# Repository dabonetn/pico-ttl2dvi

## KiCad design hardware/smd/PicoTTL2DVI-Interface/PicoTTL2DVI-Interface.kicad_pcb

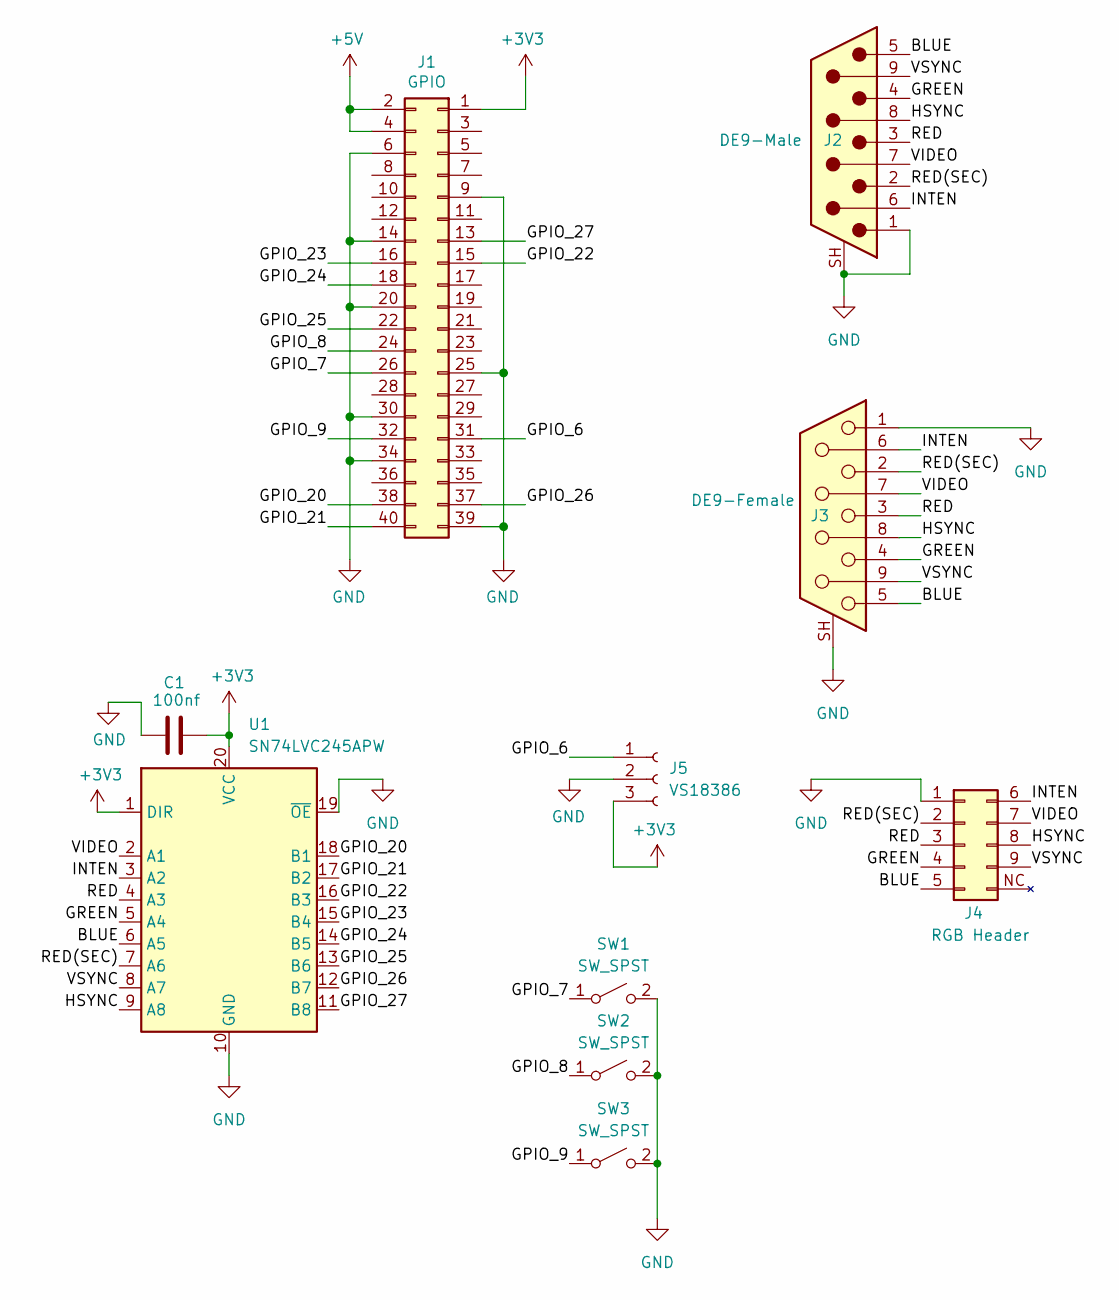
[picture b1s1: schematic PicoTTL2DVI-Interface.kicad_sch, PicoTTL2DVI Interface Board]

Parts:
C1: 100nf; C_0805_2012Metric_Pad1.18x1.45mm_HandSolder
J1: GPIO; PinSocket_2x20_P2.54mm_Vertical
J2: DE9-Male; DSUB-9_Pins_EdgeMount_P2.77mm
J3: DE9-Female; DSUB-9_Socket_EdgeMount_P2.77mm
J4: RGB Header; PinHeader_2x05_P2.54mm_Horizontal
J5: VS18386; PinHeader_1x03_P2.54mm_Vertical
SW1, SW2, SW3: SW_SPST; SW_PUSH_6mm
U1: SN74LVC245APW; TSSOP-20_4.4x6.5mm_P0.65mm

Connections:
+3V3: C1.2, J1.1, J5.3, U1.1 (DIR), U1.20 (VCC)
+5V: J1.2, J1.4
/BLUE: J2.5, J3.5, J4.5, U1.6 (A5)
/GPIO_6: J1.31, J5.1
/GPIO_7: J1.26, SW1.1 (A)
/GPIO_8: J1.24, SW2.1 (A)
/GPIO_9: J1.32, SW3.1 (A)
/GPIO_20: J1.38, U1.18 (B1)
/GPIO_21: J1.40, U1.17 (B2)
/GPIO_22: J1.15, U1.16 (B3)
/GPIO_23: J1.16, U1.15 (B4)
/GPIO_24: J1.18, U1.14 (B5)
/GPIO_25: J1.22, U1.13 (B6)
/GPIO_26: J1.37, U1.12 (B7)
/GPIO_27: J1.13, U1.11 (B8)
/GREEN: J2.4, J3.4, J4.4, U1.5 (A4)
/HSYNC: J2.8, J3.8, J4.8, U1.9 (A8)
/INTEN: J2.6, J3.6, J4.6, U1.3 (A2)
/RED: J2.3, J3.3, J4.3, U1.4 (A3)
/RED(SEC): J2.2, J3.2, J4.2, U1.7 (A6)
/VIDEO: J2.7, J3.7, J4.7, U1.2 (A1)
/VSYNC: J2.9, J3.9, J4.9, U1.8 (A7)
GND: C1.1, J1.6, J1.9, J1.14, J1.20, J1.25, J1.30, J1.34, J1.39, J2.1, J2.SH (PAD), J3.1, J3.SH (PAD), J4.1, J5.2, SW1.2 (B), SW2.2 (B), SW3.2 (B), U1.10 (GND), U1.19 (~OE)

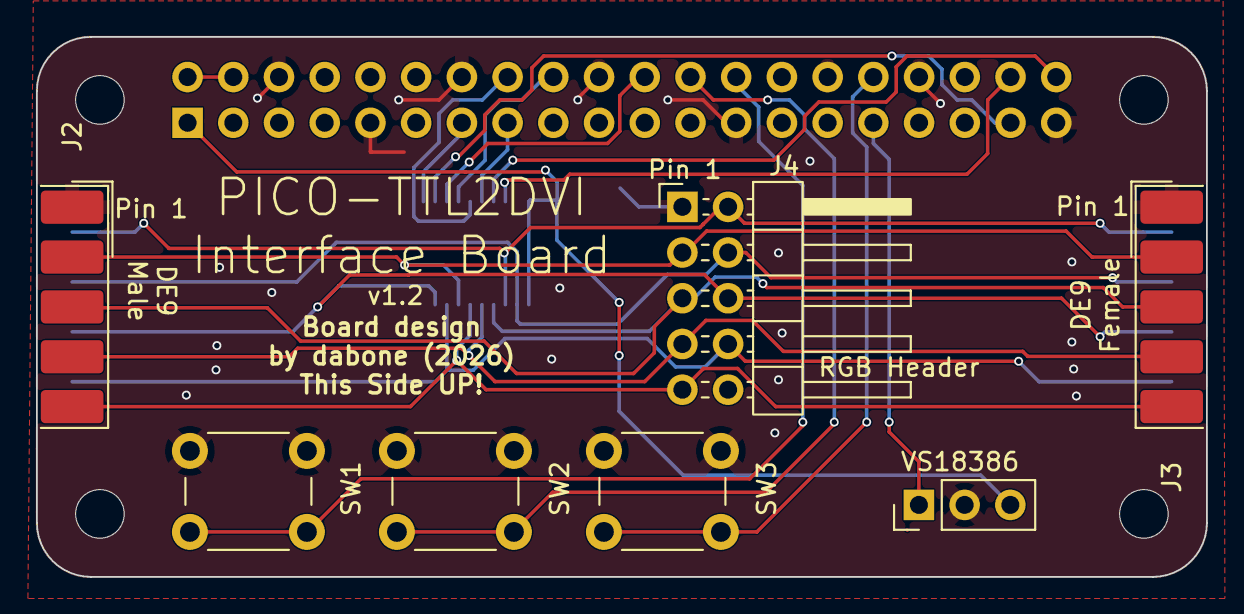
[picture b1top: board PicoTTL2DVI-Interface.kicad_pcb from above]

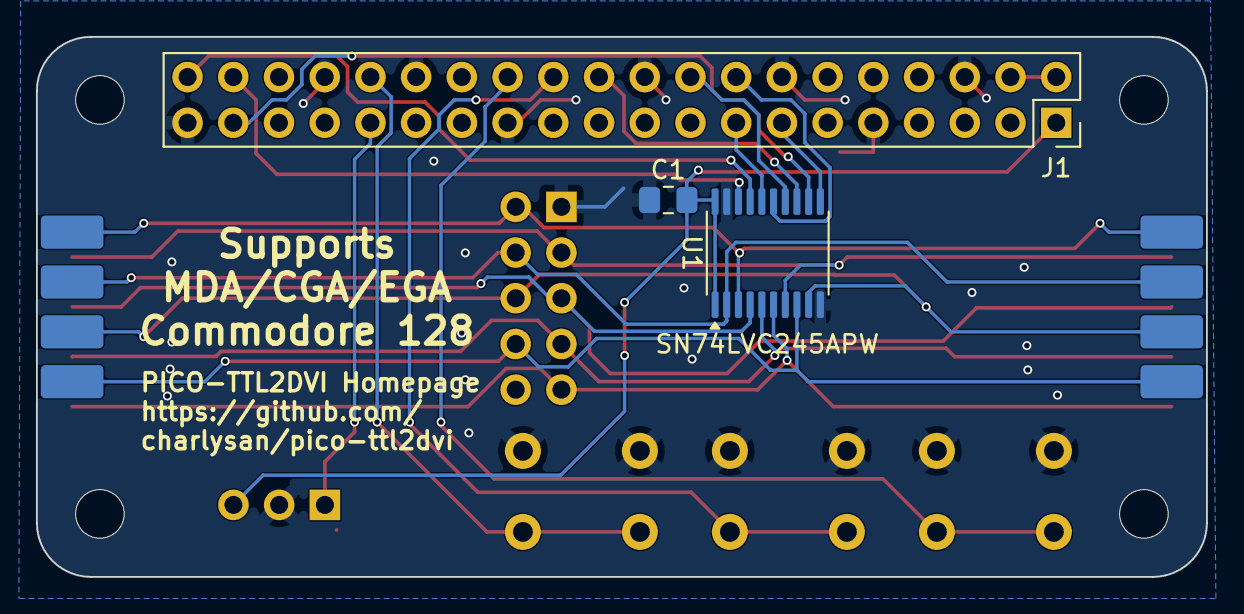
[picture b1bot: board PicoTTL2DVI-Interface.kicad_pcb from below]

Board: 2 copper layers, 65.0 x 30.0 mm, 14 parts (3 on the bottom side), 23 nets.

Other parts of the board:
MH1, MH2, MH3, MH4: MountingHole_2.7mm_M2.5

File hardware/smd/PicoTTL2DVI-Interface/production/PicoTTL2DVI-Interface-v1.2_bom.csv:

Designator,Footprint,Quantity,Value,LCSC Part #
C1,0805,1,100nf,
J1,PinSocket_2x20_P2.54mm_Vertical,1,GPIO,
J2,DSUB-9_Pins_EdgeMount_P2.77mm,1,DE9-Male,
J3,DSUB-9_Socket_EdgeMount_P2.77mm,1,DE9-Female,
J4,PinHeader_2x05_P2.54mm_Horizontal,1,RGB Header,
J5,PinHeader_1x03_P2.54mm_Vertical,1,VS18386,
"SW1, SW2, SW3",SW_PUSH_6mm,3,SW_SPST,
U1,TSSOP-20_4.4x6.5mm_P0.65mm,1,SN74LVC245APW,
